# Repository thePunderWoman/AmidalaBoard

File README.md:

# AmidalaBoard (AmidalaShield)

A custom KiCad PCB shield designed specifically for the [Amidala Firmware](https://github.com/thePunderWoman/AmidalaFirmware) — a control system for astromech and similar droid builds. This board provides all the I/O the firmware needs in a single, purpose-built package.

**Designed by [thePunderWoman](https://github.com/thePunderWoman)**

---

## Overview

The AmidalaShield is a carrier/breakout board for the **ESP32-S3 N16R8 DevKit**. It breaks out and conditions the ESP32-S3's peripherals for the specific needs of the Amidala Firmware: wireless XBee communication, multi-channel servo control, RC receiver input, SD card storage, and expansion headers for additional peripherals.

---

## Requirements

- **Microcontroller:** ESP32-S3 N16R8 DevKit (16 MB flash, 8 MB PSRAM)
- **Wireless modules:** XBee3 modules (x2 recommended — one for drive controller, one for dome controller)

---

## Hardware Features

### Wireless Communication
- **2× XBee3 module sockets** for dual-controller operation (drive + dome)

### Servo Control
- **8× PWM servo outputs** — 3-pin headers (signal, power, ground)

### Serial Ports
- **2× hardware serial ports** — UART0 (shared with USB/programming) and UART1
- **1× software serial port** — for additional peripherals

### I/O
- **6× digital I/O pins**
- **2× analog input pins**
- **1× Aux I2C header** — for external I2C devices

### RC Control
- **PPM input (ppmin)** — for analog RC receiver
- **RC select (rcsel)** — RC source selection
- **sel2** — secondary selection/mode pin

### Storage
- **Built-in microSD card reader** — used for `config.txt` at startup (matches Amidala Firmware config system)

### Expansion
- **Dedicated SPI header** — for external SPI peripherals

---

## Repository Contents

| File/Folder | Description |
|---|---|
| `AmidalaShield.kicad_sch` | Top-level schematic |
| `comms.kicad_sch` | XBee communications sub-sheet |
| `io.kicad_sch` | Digital/analog I/O sub-sheet |
| `power.kicad_sch` | Power distribution sub-sheet |
| `rc_control.kicad_sch` | RC input sub-sheet |
| `servos.kicad_sch` | Servo output sub-sheet |
| `spi.kicad_sch` | SPI header sub-sheet |
| `gerbers/` | Production-ready Gerber files |
| `libraries/` | Project-specific KiCad symbol/footprint libraries |
| `images/` | Board renders and screenshots |

---

## Getting Started

1. Clone this repo and open `AmidalaShield.kicad_pro` in KiCad 8+.
2. Review the schematics for pin assignments before assembling.
3. Use the Gerber files in `gerbers/` to order PCBs from your preferred fab.
4. Flash your ESP32-S3 with the [Amidala Firmware](https://github.com/thePunderWoman/AmidalaFirmware).
5. Place a `config.txt` on the microSD card — see the firmware repo for a full annotated example.

---

## License

This hardware design is licensed under the [Creative Commons Attribution-NonCommercial-ShareAlike 4.0 International License](LICENSE.md) (CC BY-NC-SA 4.0).

You are free to share and adapt this design for non-commercial purposes, as long as you give appropriate credit and distribute any adaptations under the same license.

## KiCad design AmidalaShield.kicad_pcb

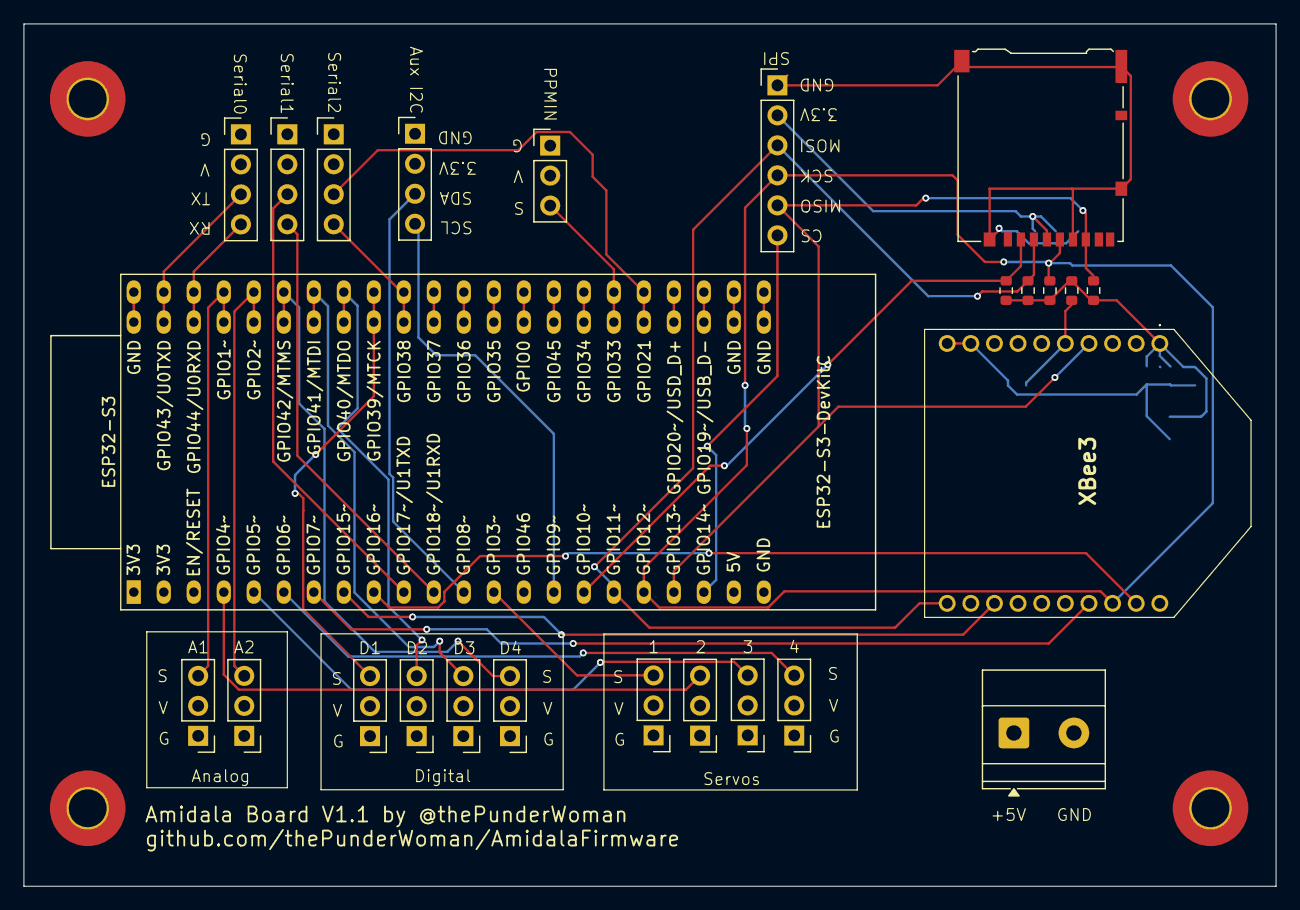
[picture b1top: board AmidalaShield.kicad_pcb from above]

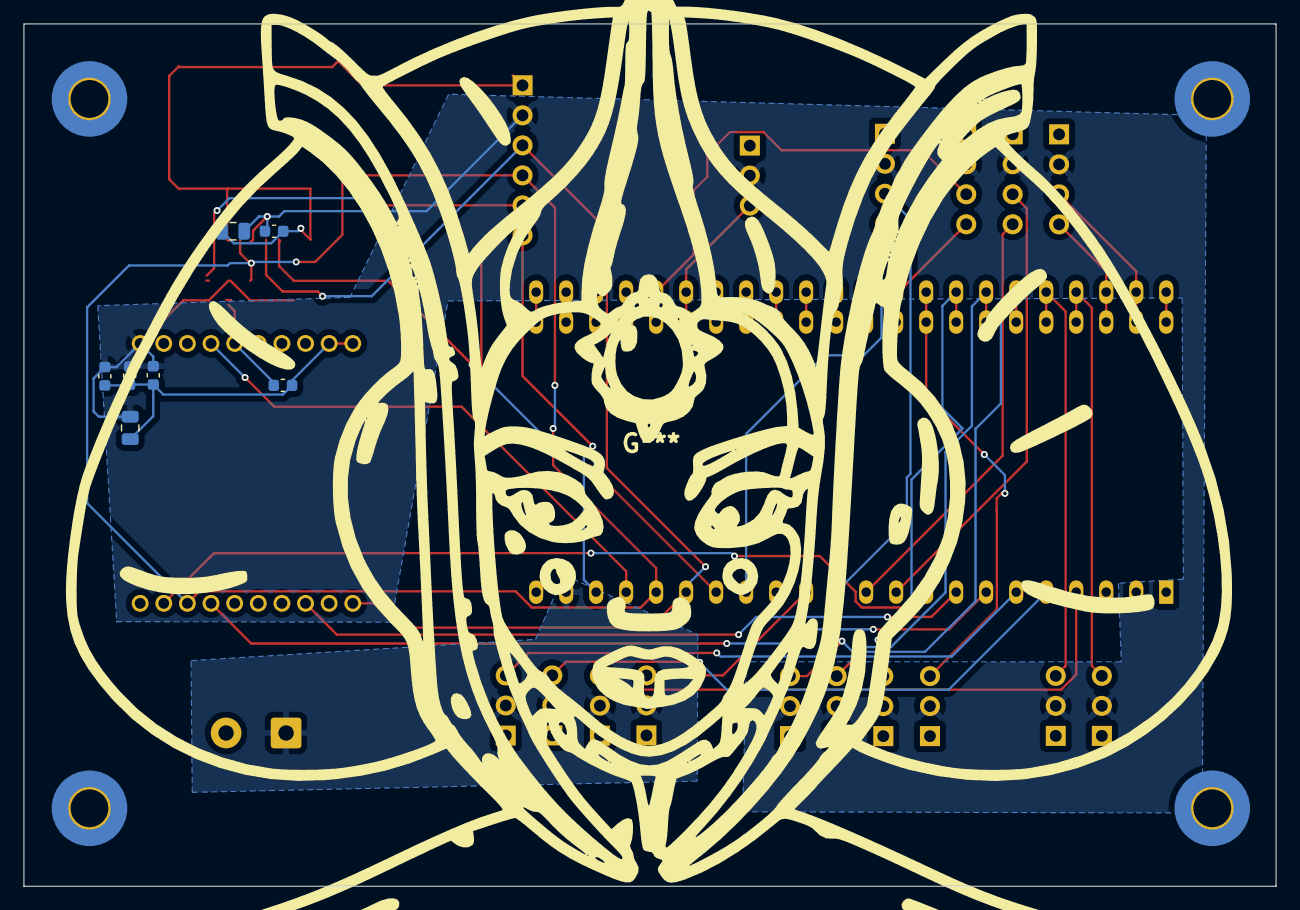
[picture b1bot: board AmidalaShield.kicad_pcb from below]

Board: 4 copper layers, 106.0 x 73.0 mm, 32 parts (7 on the bottom side), 31 nets.

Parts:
C1, C2, C3: 100n; C_0603_1608Metric
C4, C7: 10u; C_0805_2012Metric
C5: 1u; C_0603_1608Metric
C6: 8.2p; C_0603_1608Metric
ESP32-S3: ESP32-S3-DevKitC; ESP32-S2-DevKitC-1
I2C1: Aux I2C; PinHeader_1x04_P2.54mm_Vertical
J1: Screw_Terminal_01x02; TerminalBlock_Phoenix_MKDS-1,5-2-5.08_1x02_P5.08mm_Horizont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
J3: Micro_SD_Card; microSD_HC_Hirose_DM3AT-SF-PEJM5
J_Analog1: A1; PinHeader_1x03_P2.54mm_Vertical
J_Analog2: A2; PinHeader_1x03_P2.54mm_Vertical
J_Digital1: D1; PinHeader_1x03_P2.54mm_Vertical
J_Digital2: D2; PinHeader_1x03_P2.54mm_Vertical
J_Digital3: D3; PinHeader_1x03_P2.54mm_Vertical
J_Digital4: D4; PinHeader_1x03_P2.54mm_Vertical
J_PPMIN1: PPMIN; PinHeader_1x03_P2.54mm_Vertical
J_Servo1: 1; PinHeader_1x03_P2.54mm_Vertical
J_Servo2: 2; PinHeader_1x03_P2.54mm_Vertical
J_Servo3: 3; PinHeader_1x03_P2.54mm_Vertical
J_Servo4: 4; PinHeader_1x03_P2.54mm_Vertical
R1, R2, R3, R4, R5: 10k; R_0603_1608Metric
SPI1: SPI; PinHeader_1x06_P2.54mm_Vertical
SWSerial1: Serial2; PinHeader_1x04_P2.54mm_Vertical
Serial0: Serial0; PinHeader_1x04_P2.54mm_Vertical
Serial1: Serial1; PinHeader_1x04_P2.54mm_Vertical
XBee3: XB3-24Z8UT-J; XB324Z8UTJ

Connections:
+3.3V: C2.1, C3.1, C4.1, C5.1, C6.1, C7.1, I2C1.2, J3.4 (VDD), J_Analog1.2, J_Analog2.2, J_Digital1.2, J_Digital2.2, J_Digital3.2, J_Digital4.2, J_PPMIN1.2, R1.1, R2.1, R3.1, R4.1, R5.1, SPI1.2, SWSerial1.2, Serial0.2, Serial1.2, XBee3.1 (VCC)
+5V: ESP32-S3.21 (5V), J1.1, J_Servo1.2, J_Servo2.2, J_Servo3.2, J_Servo4.2
/Comms/GPIO8: ESP32-S3.12 (GPIO8/ADC1_CH7), I2C1.3
/Comms/GPIO9: ESP32-S3.15 (GPIO9/ADC1_CH8), I2C1.4
/Comms/GPIO17: ESP32-S3.10 (GPIO17/ADC2_CH6), Serial1.3
/Comms/GPIO18: ESP32-S3.11 (GPIO18/ADC2_CH7), Serial1.4
/Comms/GPIO21: ESP32-S3.27 (GPIO21), SWSerial1.3
/Comms/GPIO38: ESP32-S3.35 (GPIO38), SWSerial1.4
/Comms/GPIO43: ESP32-S3.43 (GPIO43/U0TXD), Serial0.3
/Comms/GPIO44: ESP32-S3.42 (GPIO44/U0RXD), Serial0.4
/Pins/GPIO1: ESP32-S3.41 (GPIO1/ADC1_CH0), J_Analog1.3
/Pins/GPIO2: ESP32-S3.40 (GPIO2/ADC1_CH1), J_Analog2.3
/Pins/GPIO39: ESP32-S3.36 (GPIO39/MTCK), J_Digital1.3
/Pins/GPIO40: ESP32-S3.37 (GPIO40/MTDO), J_Digital2.3
/Pins/GPIO41: ESP32-S3.38 (GPIO41/MTDI), J_Digital3.3
/Pins/GPIO42: ESP32-S3.39 (GPIO42/MTMS), J_Digital4.3
/RC Control/GPIO47: ESP32-S3.28 (GPIO47), J_PPMIN1.3
/SPI/GPIO7: ESP32-S3.7 (GPIO7/ADC1_CH6), XBee3.17 (AD3/DIO3/SPI_~SSEL)
/SPI/GPIO10: ESP32-S3.16 (GPIO10/ADC1_CH9), J3.2 (DAT3/CD), R2.2
/SPI/GPIO11: ESP32-S3.17 (GPIO11/ADC2_CH0), J3.3 (CMD), R3.2, SPI1.3, XBee3.11 (DIO4/SPI_MOSI)
/SPI/GPIO12: ESP32-S3.18 (GPIO12/ADC2_CH1), J3.5 (CLK), R4.2, SPI1.4, XBee3.18 (AD2/DIO2/SPI_CLK)
/SPI/GPIO13: ESP32-S3.19 (GPIO13/ADC2_CH2), J3.7 (DAT0), R5.2, SPI1.5, XBee3.4 (DIO12/SPI_MISO)
/SPI/GPIO14: ESP32-S3.20 (GPIO14/ADC2_CH3), SPI1.6
/SPI/GPIO15: ESP32-S3.8 (GPIO15/ADC2_CH4/32K_P), XBee3.13 (ON/~SLEEP/DIO9)
/SPI/GPIO16: ESP32-S3.9 (GPIO16/ADC2_CH5/32K_N), XBee3.19 (AD1/DIO1/SPI_~ATTN)
/Servos/GPIO3: ESP32-S3.13 (GPIO3/ADC1_CH2), J_Servo1.3
/Servos/GPIO4: ESP32-S3.4 (GPIO4/ADC1_CH3), J_Servo2.3
/Servos/GPIO5: ESP32-S3.5 (GPIO5/ADC1_CH4), J_Servo3.3
/Servos/GPIO6: ESP32-S3.6 (GPIO6/ADC1_CH5), J_Servo4.3
GND: C1.2, C2.2, C3.2, C4.2, C5.2, C6.2, C7.2, ESP32-S3.22 (GND), ESP32-S3.23 (GND), ESP32-S3.24 (GND), ESP32-S3.44 (GND), I2C1.1, J1.2, J3.6 (VSS), J3.11 (SHIELD), J_Analog1.1, J_Analog2.1, J_Digital1.1, J_Digital2.1, J_Digital3.1, J_Digital4.1, J_PPMIN1.1, J_Servo1.1, J_Servo2.1, J_Servo3.1, J_Servo4.1, SPI1.1, SWSerial1.1, Serial0.1, Serial1.1, XBee3.9 (~DTR/SLEEP_RQ/DIO8), XBee3.10 (GND)
unnamed: C1.1, R1.2, XBee3.5 (~RESET)

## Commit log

2026-05-03 added readme
2026-05-03 Switched SD Card slots
2026-05-03 Remapped GPIOs for clean routing
    This updates the GPIO table so that the traces and vias are far cleaner. Slight repositioning of some pins to account for that. Rebuilt all gerbers and necessary stuff.
2026-05-03 final pass safety check
    This verified that the XBee had all the pins wired up correctly with the proper resistor and cap connections. Glad I caught this before getting them fabbed.
2026-05-23 Updated to v1.1 to fix issues
2026-06-12 Updated to v1.2 to address remaining issues
